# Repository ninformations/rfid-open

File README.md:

# rfid

This is a 125Khz rfid project using RDM6300, Pro Micro nrf52840 and Wio SX1262 to read and transmit rfid d to a controller on meshtastic network

Created by Astami Vishwakarma <astami@shipperstack.com>

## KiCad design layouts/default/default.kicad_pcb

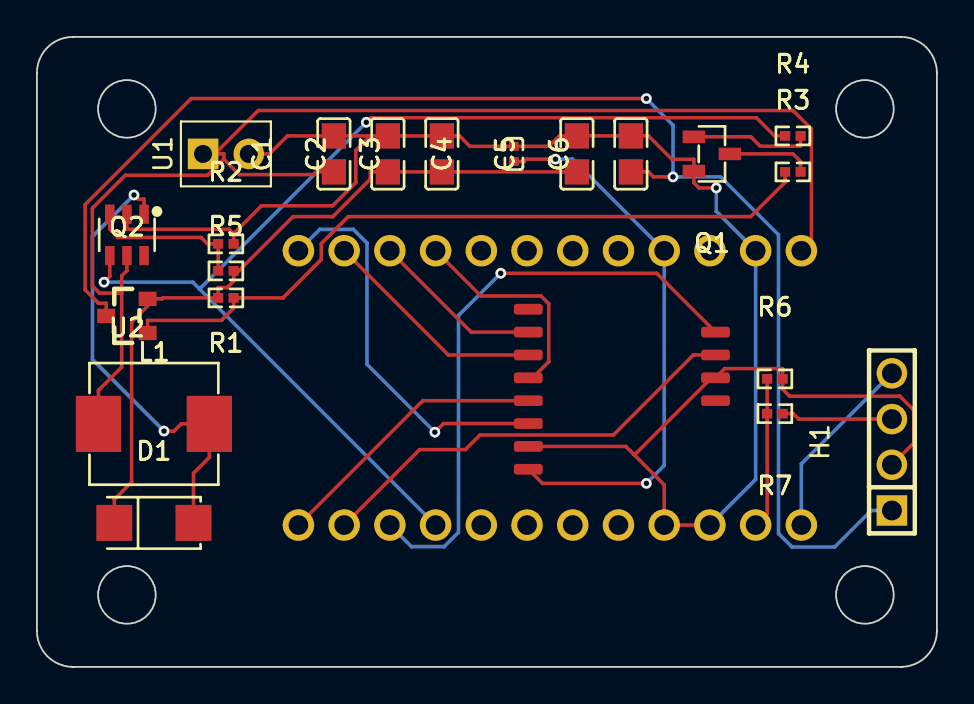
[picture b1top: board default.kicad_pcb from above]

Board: 2 copper layers, 50.0 x 35.0 mm, 22 parts (1 on the bottom side), 21 nets.

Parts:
C1, C2, C3: 22µF ±20% 25V X5R; C0805
C4: 100nF ±10% 16V X7R; C0402
C5: 47µF ±20% 6.3V X5R; C0805
C6: 10µF ±10% 25V X5R; C0805
D1: SMA_L4.3-W2.6-LS5.2-RD
H1: HDR-TH_4P-P2.54-V-M
L1: 22µH ±20% 135mΩ; IND-SMD_L7.3-W6.6_MHCI06030
Q1: SOT-23-3_L2.9-W1.3-P1.90-LS2.4-BR
Q2: SOT-23_L2.9-W1.3-P1.90-LS2.4-BR
R1: 220kΩ ±1% 62.5mW; R0402
R2: 30kΩ ±1% 62.5mW; R0402
R3: 10kΩ ±1% 62.5mW; R0402
R4, R5: 1MΩ ±1% 62.5mW; R0402
R6: 200kΩ ±1% 62.5mW; R0402
R7: 100kΩ ±1% 62.5mW; R0402
U1: HDR-TH_2P-P2.54-V
U2: SOT-23-6_L2.9-W1.6-P0.95-LS2.8-BL
U3: WioSX1262
U4: ProMicro_nRF52840

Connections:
A: D1.2, L1.2, U2.1
D: Q1.3, R3.2
FB: R1.2, R2.1, U2.3
GND: C1.2, C2.2, C3.2, C4.2, C5.2, C6.2, H1.2, Q1.2, R2.2, R6.2, U1.2, U2.2, U3.7, U3.10, U4.3, U4.4, U4.23
MISO: U3.2, U4.15
MOSI: U3.3, U4.14
SCLK: U3.4, U4.16
TX: H1.4, U4.1
busy: U3.11, U4.11
cs: U3.6, U4.13
dio1: U3.12, U4.10
enable: R4.1, U2.4, U4.9
footprint-G-0: Q1.1, R4.2
footprint-G-1: Q2.1, R3.1, R5.2
footprint-reset-0: U3.5, U4.12
mcu-uart-RX: R6.1, R7.2, U4.2
power_gnd-VCC: C4.1, U3.8, U4.21
power_in-VCC: C2.1, C3.1, C5.1, D1.1, Q2.2, R1.1, R5.1
power_out-VCC: C6.1, H1.1, Q2.3
power_raw-VCC: C1.1, L1.1, U1.1, U2.5, U4.24
rfid-uart-RX: H1.3, R7.1
